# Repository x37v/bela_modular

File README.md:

# bela_modular

A modular level interface for the bela beagle bone black cape, kicad projects.

[bela](http://bela.io/) is a cape for the beagle bone black

* based off the [audio expansion cape](http://blog.bela.io/analogue-vs-digital/)
* [hardware info](https://github.com/BelaPlatform/Bela/wiki/Hardware-explained)

## Pin mappings

The digital i/o is mapped as such:

|Bela #|	 Board            | Note 	             |
|------|---------           | -------------------|
|00    |  in 1              ||
|01    |  in 2              ||
|02    |  in 3              ||
|03    |  in 4              ||
|04    |  digtial in enable | pull low to enable |
|05    |  vfd ctrl enable   | pull low to enable |
|06    |  encin2-btn        ||
|07    |  encin2-b          ||
|08    |  out 1             ||
|09    |  out 2             ||
|10    |  encin2-a          ||
|11    |  out 3             ||
|12    |  out 5             ||
|13    |  out 4             ||
|14    |  out 7             ||
|15    |  out 6             ||

### VFD IO

| P8 |                      | gpio | note                    |
|:--:|----------------------|------|--                       |
| 12 | ctrl enable          | 1_12 | mapped in bela software |
| 14 | digital out enable   | 0_26 |      |
| 31 | P busy in            | 0_10 |      |
| 34 | vDE                  | 2_17 |      |
| 35 | CS2                  | 0_8  |      |
| 36 | CS1                  | 2_16 |      |
| 37 | /RD and RW           | 2_14 |      |
| 38 | /WR and RS           | 2_15 |      |
|    |                      |      |      |
| 39 | D7                   | 2_12 |      |
| 40 | D6                   | 2_13 |      |
| 41 | D5                   | 2_10 |      |
| 42 | D4                   | 2_11 |      |
| 43 | D3                   | 2_8  |      |
| 44 | D2                   | 2_9  |      |
| 45 | D1                   | 2_6  |      |
| 46 | D0                   | 2_7  |      |

### Errors/rework

The digital 'extra' board from 3/17 requires a rework for the digital out and
control enable pins [P8 12 and 14]. These should be detached from 5V and
attached to 3.3V.

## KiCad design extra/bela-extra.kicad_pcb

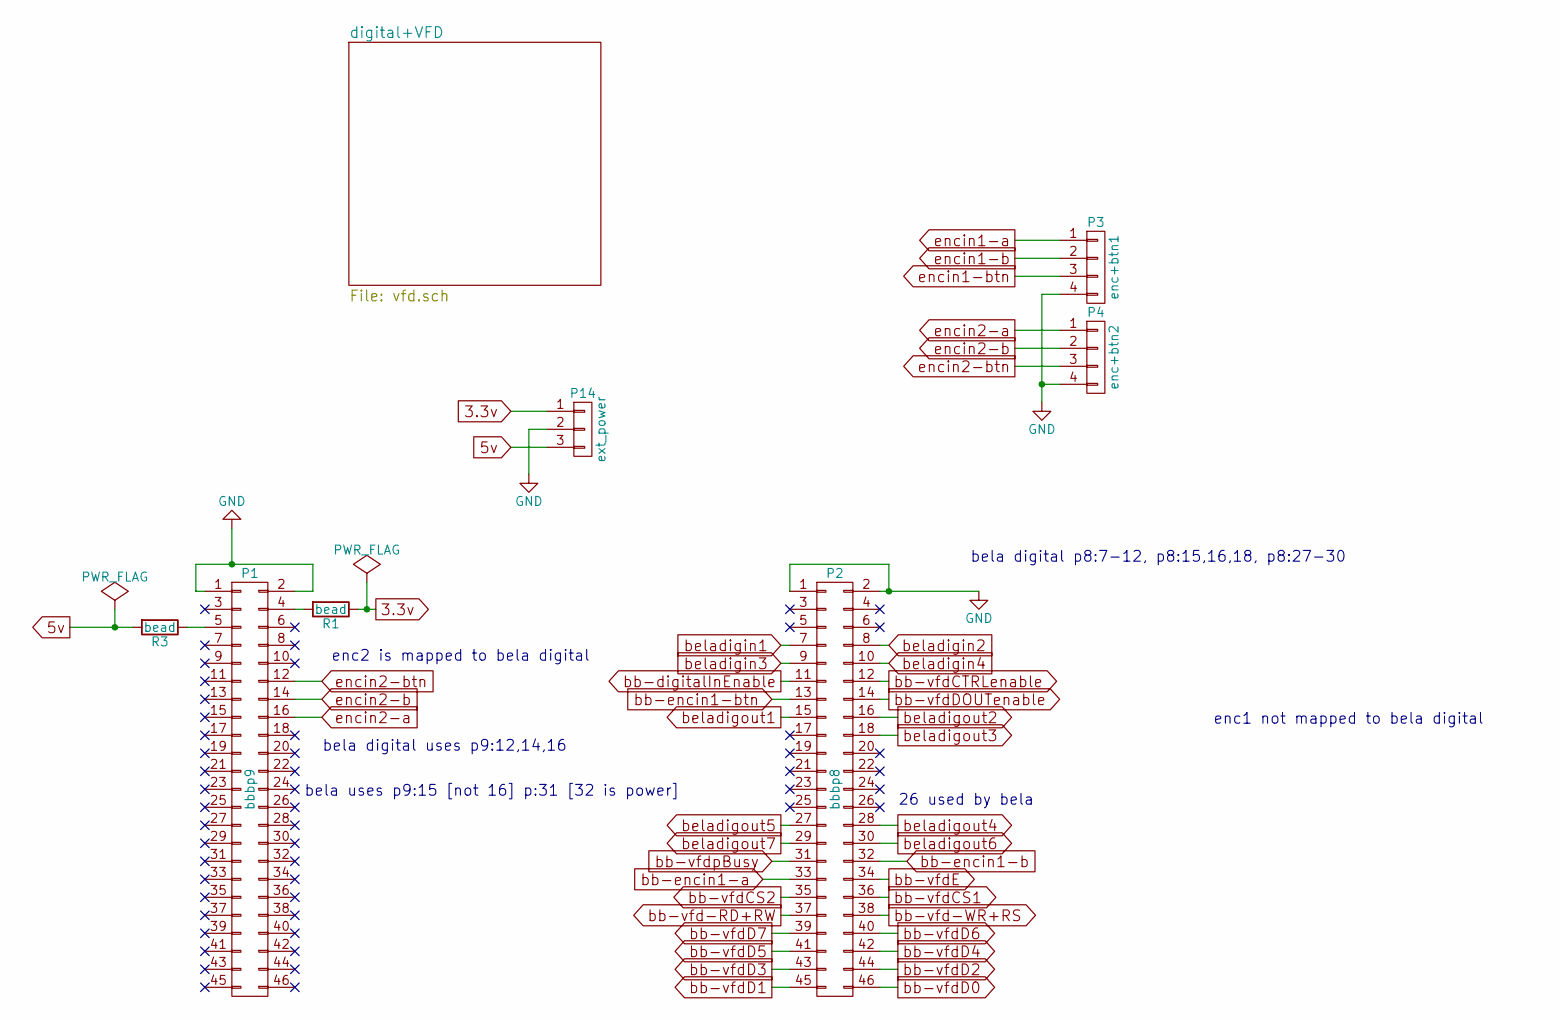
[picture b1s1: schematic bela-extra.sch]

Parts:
P1: bbbp9; Pin_Header_Straight_2x23_Pitch2.54mm
P2: bbbp8; Pin_Header_Straight_2x23_Pitch2.54mm
P3: enc+btn1; Pin_Header_Straight_1x04_Pitch2.54mm
P4: enc+btn2; Pin_Header_Straight_1x04_Pitch2.54mm
P14: ext_power; Pin_Header_Straight_1x03_Pitch2.54mm
R1, R3: bead; Resistor_Vertical_RM5mm-xnor

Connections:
3.3v: P14.1, R1.1; also elsewhere on the board
5v: P14.3, R3.2; also elsewhere on the board
GND: P1.1, P1.2, P2.1, P2.2, P3.4, P4.4, P14.2; also elsewhere on the board
unnamed: P1.4, R1.2
unnamed: P1.5, R3.1
bb-digitalInEnable: P2.11; also elsewhere on the board
bb-encin1-a: P2.33; also elsewhere on the board
bb-encin1-b: P2.32; also elsewhere on the board
bb-encin1-btn: P2.13; also elsewhere on the board
bb-vfd-RD+RW: P2.37; also elsewhere on the board
bb-vfd-WR+RS: P2.38; also elsewhere on the board
bb-vfdCS1: P2.36; also elsewhere on the board
bb-vfdCS2: P2.35; also elsewhere on the board
bb-vfdCTRLenable: P2.12; also elsewhere on the board
bb-vfdD0: P2.46; also elsewhere on the board
bb-vfdD1: P2.45; also elsewhere on the board
bb-vfdD2: P2.44; also elsewhere on the board
bb-vfdD3: P2.43; also elsewhere on the board
bb-vfdD4: P2.42; also elsewhere on the board
bb-vfdD5: P2.41; also elsewhere on the board
bb-vfdD6: P2.40; also elsewhere on the board
bb-vfdD7: P2.39; also elsewhere on the board
bb-vfdDOUTenable: P2.14; also elsewhere on the board
bb-vfdE: P2.34; also elsewhere on the board
bb-vfdpBusy: P2.31; also elsewhere on the board
beladigin1: P2.7; also elsewhere on the board
beladigin2: P2.8; also elsewhere on the board
beladigin3: P2.9; also elsewhere on the board
beladigin4: P2.10; also elsewhere on the board
beladigout1: P2.15; also elsewhere on the board
beladigout2: P2.16; also elsewhere on the board
beladigout3: P2.18; also elsewhere on the board
beladigout4: P2.28; also elsewhere on the board
beladigout5: P2.27; also elsewhere on the board
beladigout6: P2.30; also elsewhere on the board
beladigout7: P2.29; also elsewhere on the board
encin1-a: P3.1; also elsewhere on the board
encin1-b: P3.2; also elsewhere on the board
encin1-btn: P3.3; also elsewhere on the board
encin2-a: P1.16, P4.1
encin2-b: P1.14, P4.2
encin2-btn: P1.12, P4.3

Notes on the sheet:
enc1 not mapped to bela digital
enc2 is mapped to bela digital
26 used by bela
bela uses p9:15 [not 16] p:31 [32 is power]
bela digital p8:7-12, p8:15,16,18, p8:27-30
bela digital uses p9:12,14,16

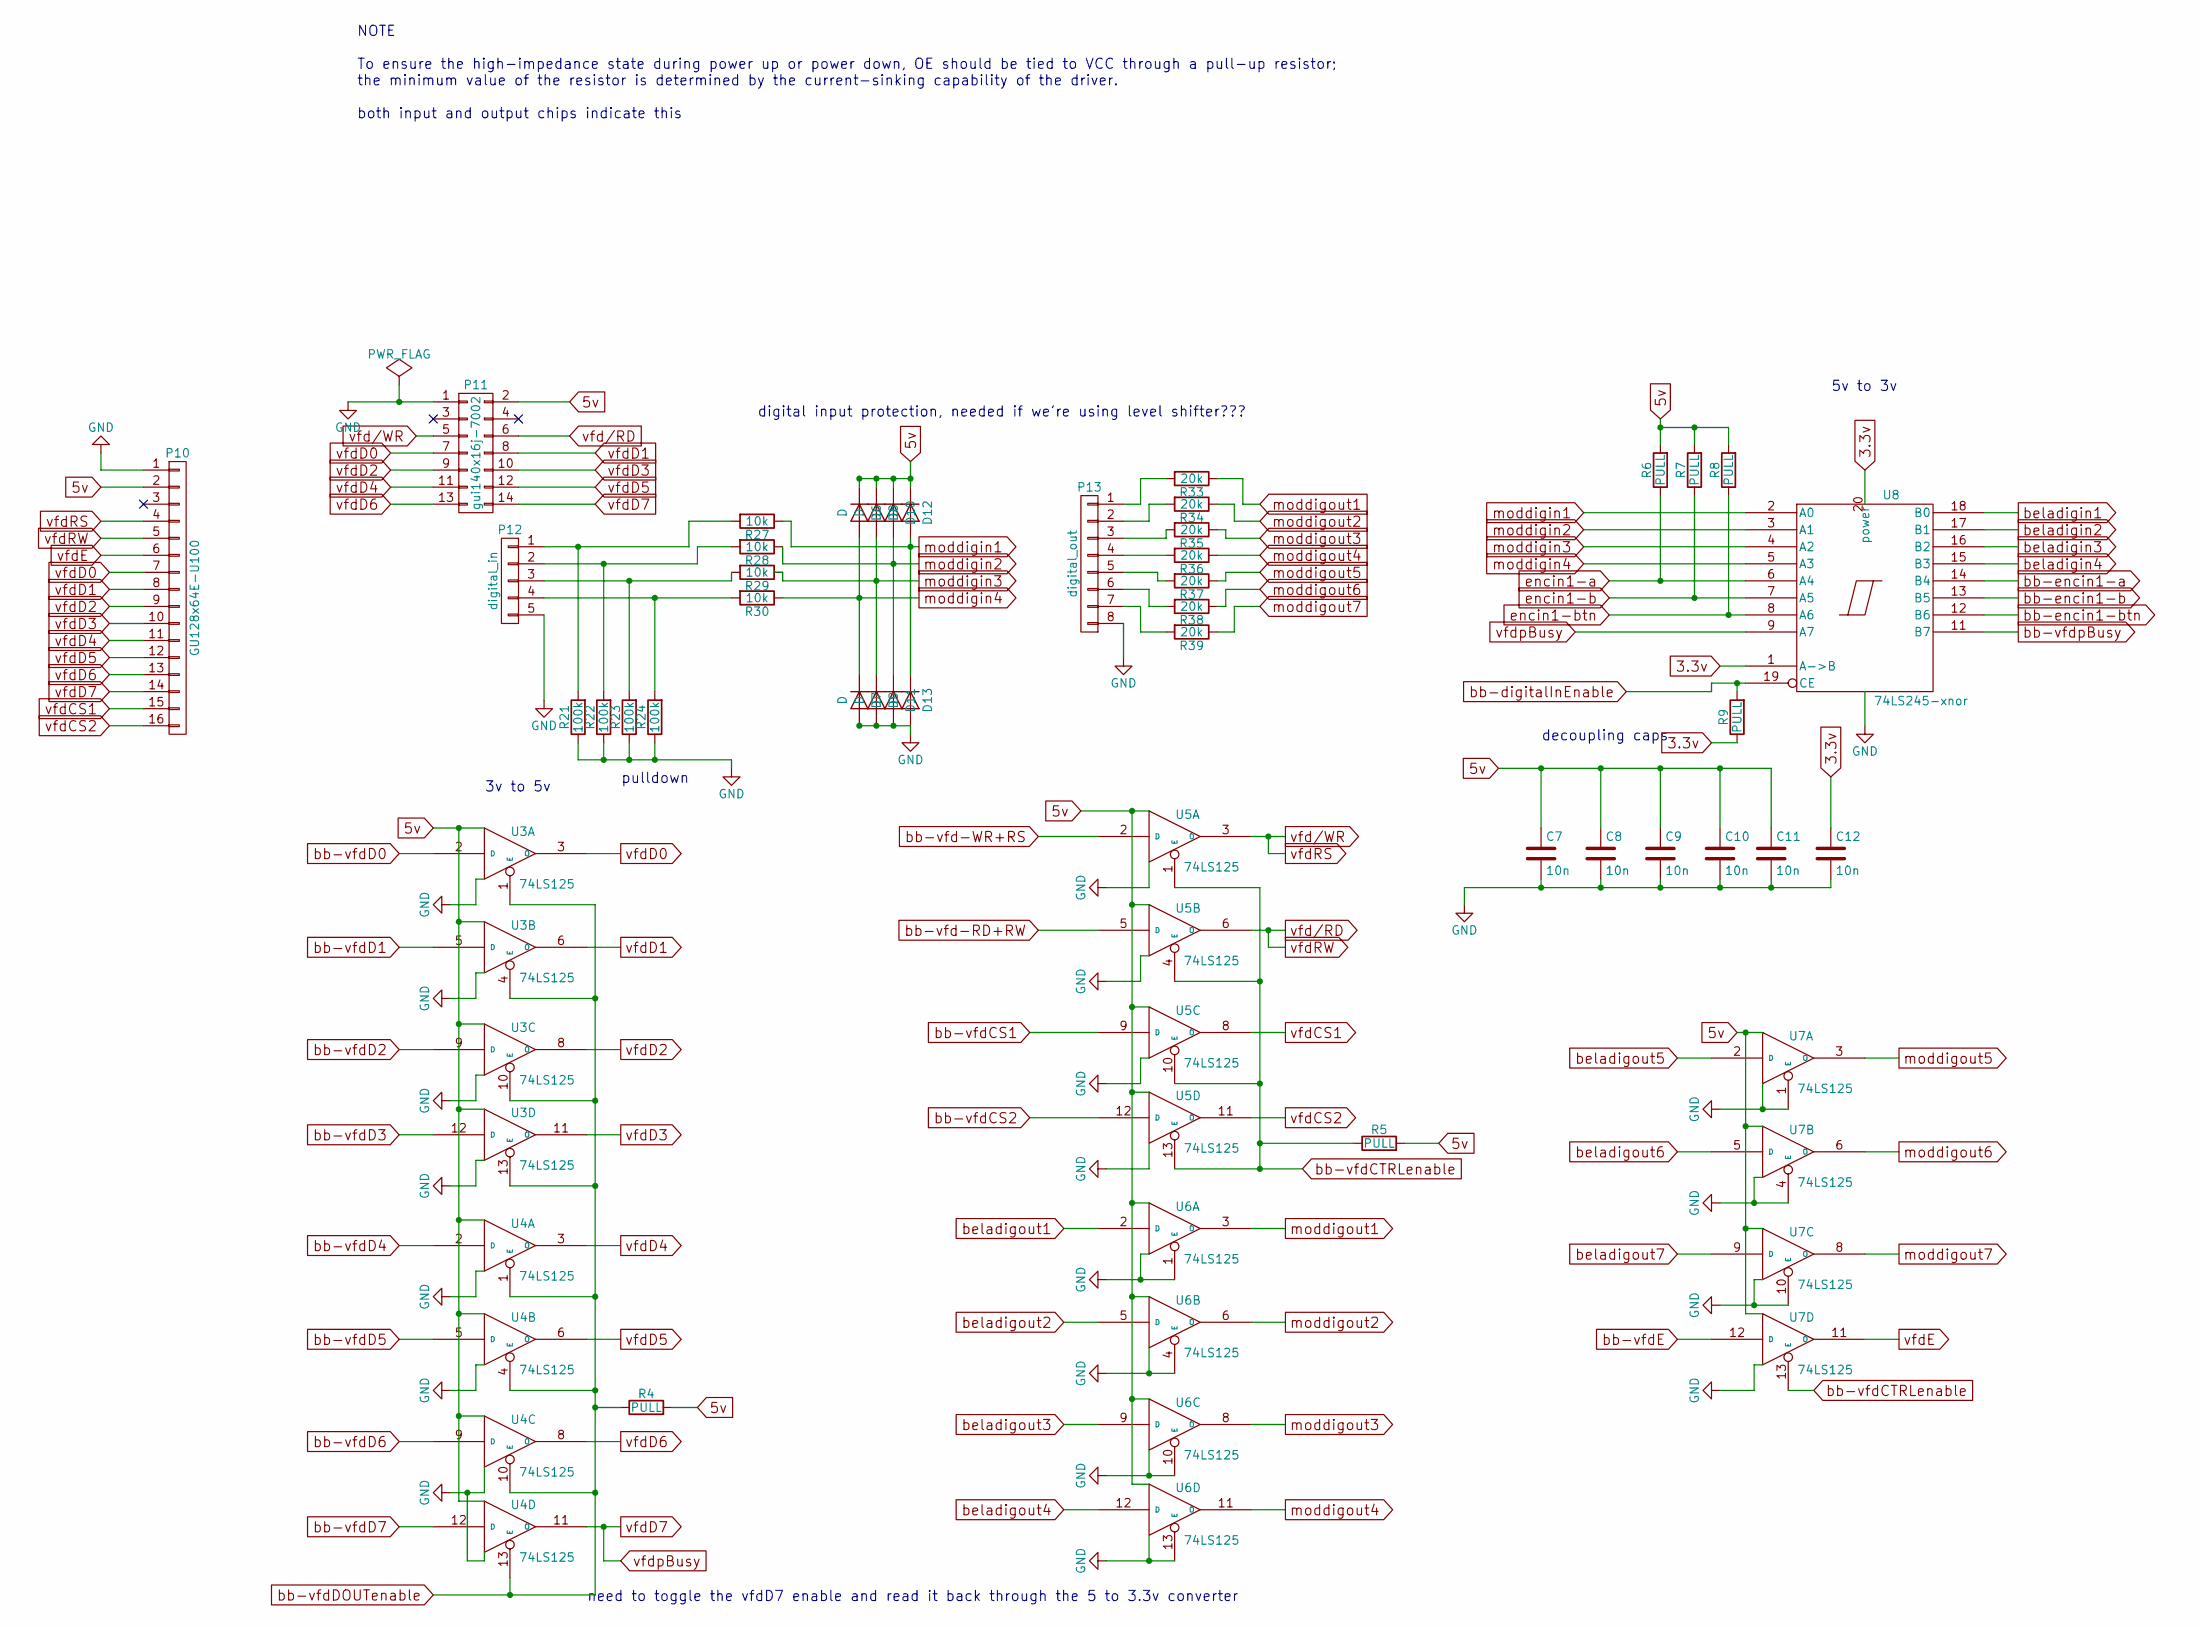
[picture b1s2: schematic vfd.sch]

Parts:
C7, C8, C9, C10, C11, C12: 10n; C_Rect_L4_W2.5_P2.5
D6, D7, D8, D9, D10, D11, D12, D13: D; D_DO-41_SOD81_P7.62mm_Horizontal
P10: GU128x64E-U100; Pin_Header_Straight_1x16_Pitch2.54mm
P11: gui140x16j-7002; Pin_Header_Straight_2x07_Pitch2.54mm
P12: digital_in; Pin_Header_Straight_1x05_Pitch2.54mm
P13: digital_out; Pin_Header_Straight_1x08_Pitch2.54mm
R4, R5, R6, R7, R8, R9: PULL; Resistor_Horizontal_RM10mm-xnorman
R21, R22, R23, R24: 100k; Resistor_Horizontal_RM10mm-xnorman
R27, R28, R29, R30: 10k; Resistor_Horizontal_RM10mm-xnorman
R33, R34, R35, R36, R37, R38, R39: 20k; Resistor_Horizontal_RM10mm-xnorman
U3, U4, U5, U6, U7: 74LS125; DIP-14_W7.62mm_LongPads
U8: 74LS245-xnor; DIP-20_W7.62mm_LongPads

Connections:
3.3v: C12.1, R9.1, U8.1 (A->B), U8.20 (power); also elsewhere on the board
5v: C7.1, C8.1, C9.1, C10.1, C11.1, D6.1 (K), D8.1 (K), D10.1 (K), D12.1 (K), P10.2, P11.2, R4.2, R5.2, R6.2, R7.2, R8.2, U3.14 (VCC), U4.14 (VCC), U5.14 (VCC), U6.14 (VCC), U7.14 (VCC); also elsewhere on the board
GND: C7.2, C8.2, C9.2, C10.2, C11.2, C12.2, D7.2 (A), D9.2 (A), D11.2 (A), D13.2 (A), P10.1, P11.1, P12.5, P13.8, R21.1, R22.1, R23.1, R24.1, U3.7 (GND), U4.7 (GND), U5.7 (GND), U6.1 (E), U6.4 (E), U6.7 (GND), U6.10 (E), U6.13 (E), U7.1 (E), U7.4 (E), U7.7 (GND), U7.10 (E), U8.10 (GND); also elsewhere on the board
unnamed: P12.1, R21.2, R27.2
unnamed: P12.2, R22.2, R28.2
unnamed: P12.3, R23.2, R29.2
unnamed: P12.4, R24.2, R30.2
unnamed: P13.1, R33.2
unnamed: P13.2, R34.2
unnamed: P13.3, R35.2
unnamed: P13.4, R36.2
unnamed: P13.5, R37.2
unnamed: P13.6, R38.2
unnamed: P13.7, R39.2
bb-digitalInEnable: R9.2, U8.19 (CE); also elsewhere on the board
bb-encin1-a: U8.14 (B4); also elsewhere on the board
bb-encin1-b: U8.13 (B5); also elsewhere on the board
bb-encin1-btn: U8.12 (B6); also elsewhere on the board
bb-vfd-RD+RW: U5.5 (D); also elsewhere on the board
bb-vfd-WR+RS: U5.2 (D); also elsewhere on the board
bb-vfdCS1: U5.9 (D); also elsewhere on the board
bb-vfdCS2: U5.12 (D); also elsewhere on the board
bb-vfdCTRLenable: R5.1, U5.1 (E), U5.4 (E), U5.10 (E), U5.13 (E), U7.13 (E); also elsewhere on the board
bb-vfdD0: U3.2 (D); also elsewhere on the board
bb-vfdD1: U3.5 (D); also elsewhere on the board
bb-vfdD2: U3.9 (D); also elsewhere on the board
bb-vfdD3: U3.12 (D); also elsewhere on the board
bb-vfdD4: U4.2 (D); also elsewhere on the board
bb-vfdD5: U4.5 (D); also elsewhere on the board
bb-vfdD6: U4.9 (D); also elsewhere on the board
bb-vfdD7: U4.12 (D); also elsewhere on the board
bb-vfdDOUTenable: R4.1, U3.1 (E), U3.4 (E), U3.10 (E), U3.13 (E), U4.1 (E), U4.4 (E), U4.10 (E), U4.13 (E); also elsewhere on the board
bb-vfdE: U7.12 (D); also elsewhere on the board
bb-vfdpBusy: U8.11 (B7); also elsewhere on the board
beladigin1: U8.18 (B0); also elsewhere on the board
beladigin2: U8.17 (B1); also elsewhere on the board
beladigin3: U8.16 (B2); also elsewhere on the board
beladigin4: U8.15 (B3); also elsewhere on the board
beladigout1: U6.2 (D); also elsewhere on the board
beladigout2: U6.5 (D); also elsewhere on the board
beladigout3: U6.9 (D); also elsewhere on the board
beladigout4: U6.12 (D); also elsewhere on the board
beladigout5: U7.2 (D); also elsewhere on the board
beladigout6: U7.5 (D); also elsewhere on the board
beladigout7: U7.9 (D); also elsewhere on the board
encin1-a: R6.1, U8.6 (A4); also elsewhere on the board
encin1-b: R7.1, U8.7 (A5); also elsewhere on the board
encin1-btn: R8.1, U8.8 (A6); also elsewhere on the board
moddigin1: D12.2 (A), D13.1 (K), R27.1, U8.2 (A0)
moddigin2: D10.2 (A), D11.1 (K), R28.1, U8.3 (A1)
moddigin3: D8.2 (A), D9.1 (K), R29.1, U8.4 (A2)
moddigin4: D6.2 (A), D7.1 (K), R30.1, U8.5 (A3)
moddigout1: R33.1, U6.3 (O)
moddigout2: R34.1, U6.6 (O)
moddigout3: R35.1, U6.8 (O)
moddigout4: R36.1, U6.11 (O)
moddigout5: R37.1, U7.3 (O)
moddigout6: R38.1, U7.6 (O)
moddigout7: R39.1, U7.8 (O)
vfd/RD: P10.5, P11.6, U5.6 (O)
vfd/WR: P10.4, P11.5, U5.3 (O)
vfdCS1: P10.15, U5.8 (O)
vfdCS2: P10.16, U5.11 (O)
vfdD0: P10.7, P11.7, U3.3 (O)
vfdD1: P10.8, P11.8, U3.6 (O)
vfdD2: P10.9, P11.9, U3.8 (O)
vfdD3: P10.10, P11.10, U3.11 (O)
vfdD4: P10.11, P11.11, U4.3 (O)
vfdD5: P10.12, P11.12, U4.6 (O)
vfdD6: P10.13, P11.13, U4.8 (O)
vfdD7: P10.14, P11.14, U4.11 (O), U8.9 (A7)
vfdE: P10.6, U7.11 (O)

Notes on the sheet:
3v to 5v
5v to 3v
need to toggle the vfdD7 enable and read it back through the 5 to 3.3v converter
NOTE To ensure the high-impedance state during power up or power down, OE should be tied to VCC through a pull-up resistor; the minimum value of the resistor is determined by the current-sinking capability of the driver. both input and output chips indicate this
digital input protection, needed if we're using level shifter???
pulldown
decoupling caps

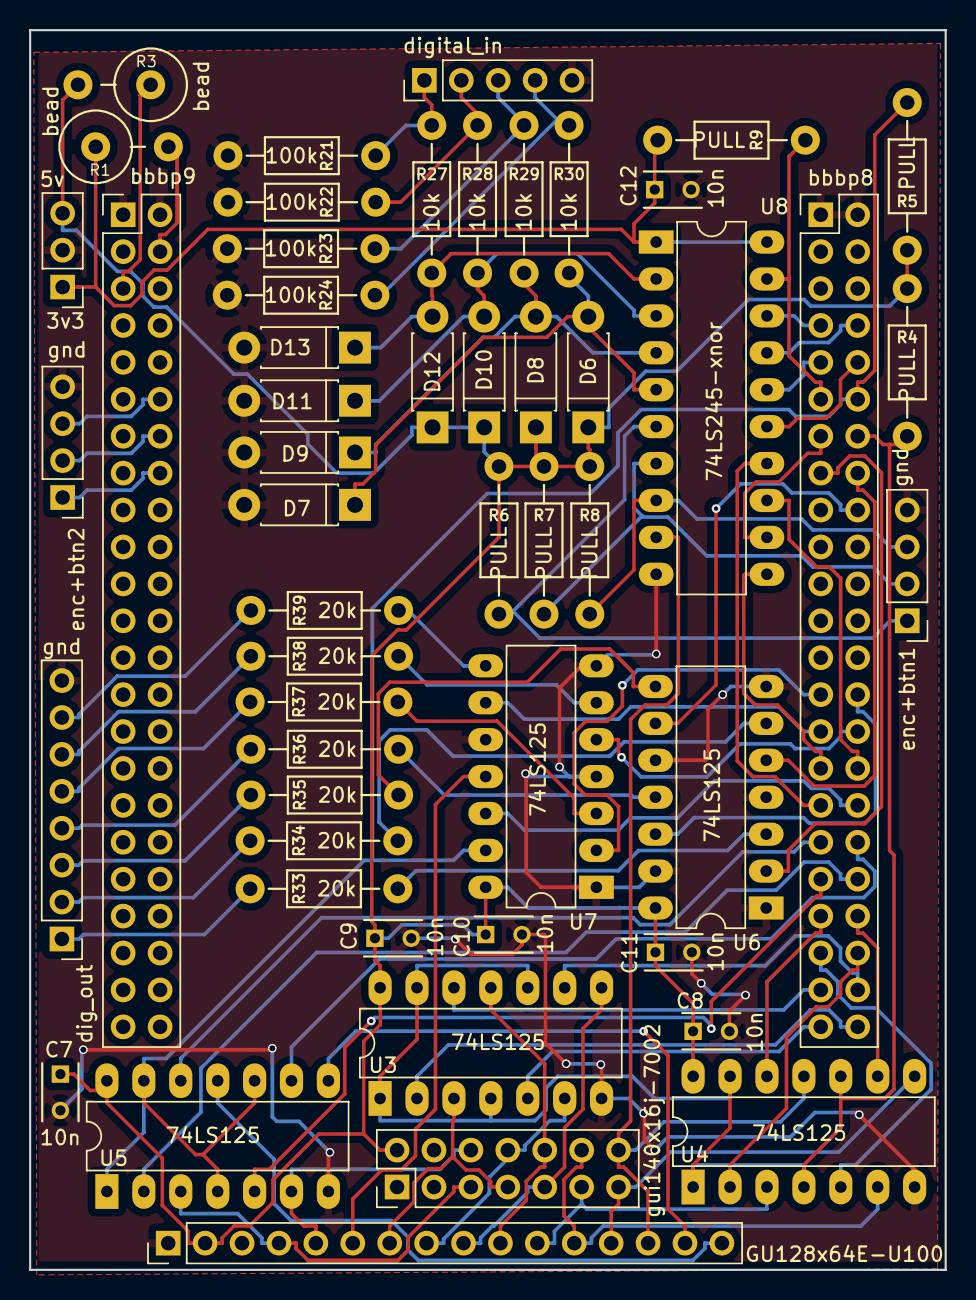
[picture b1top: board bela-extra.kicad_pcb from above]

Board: 2 copper layers, 63.0 x 85.3 mm, 52 parts (0 on the bottom side), 77 nets.

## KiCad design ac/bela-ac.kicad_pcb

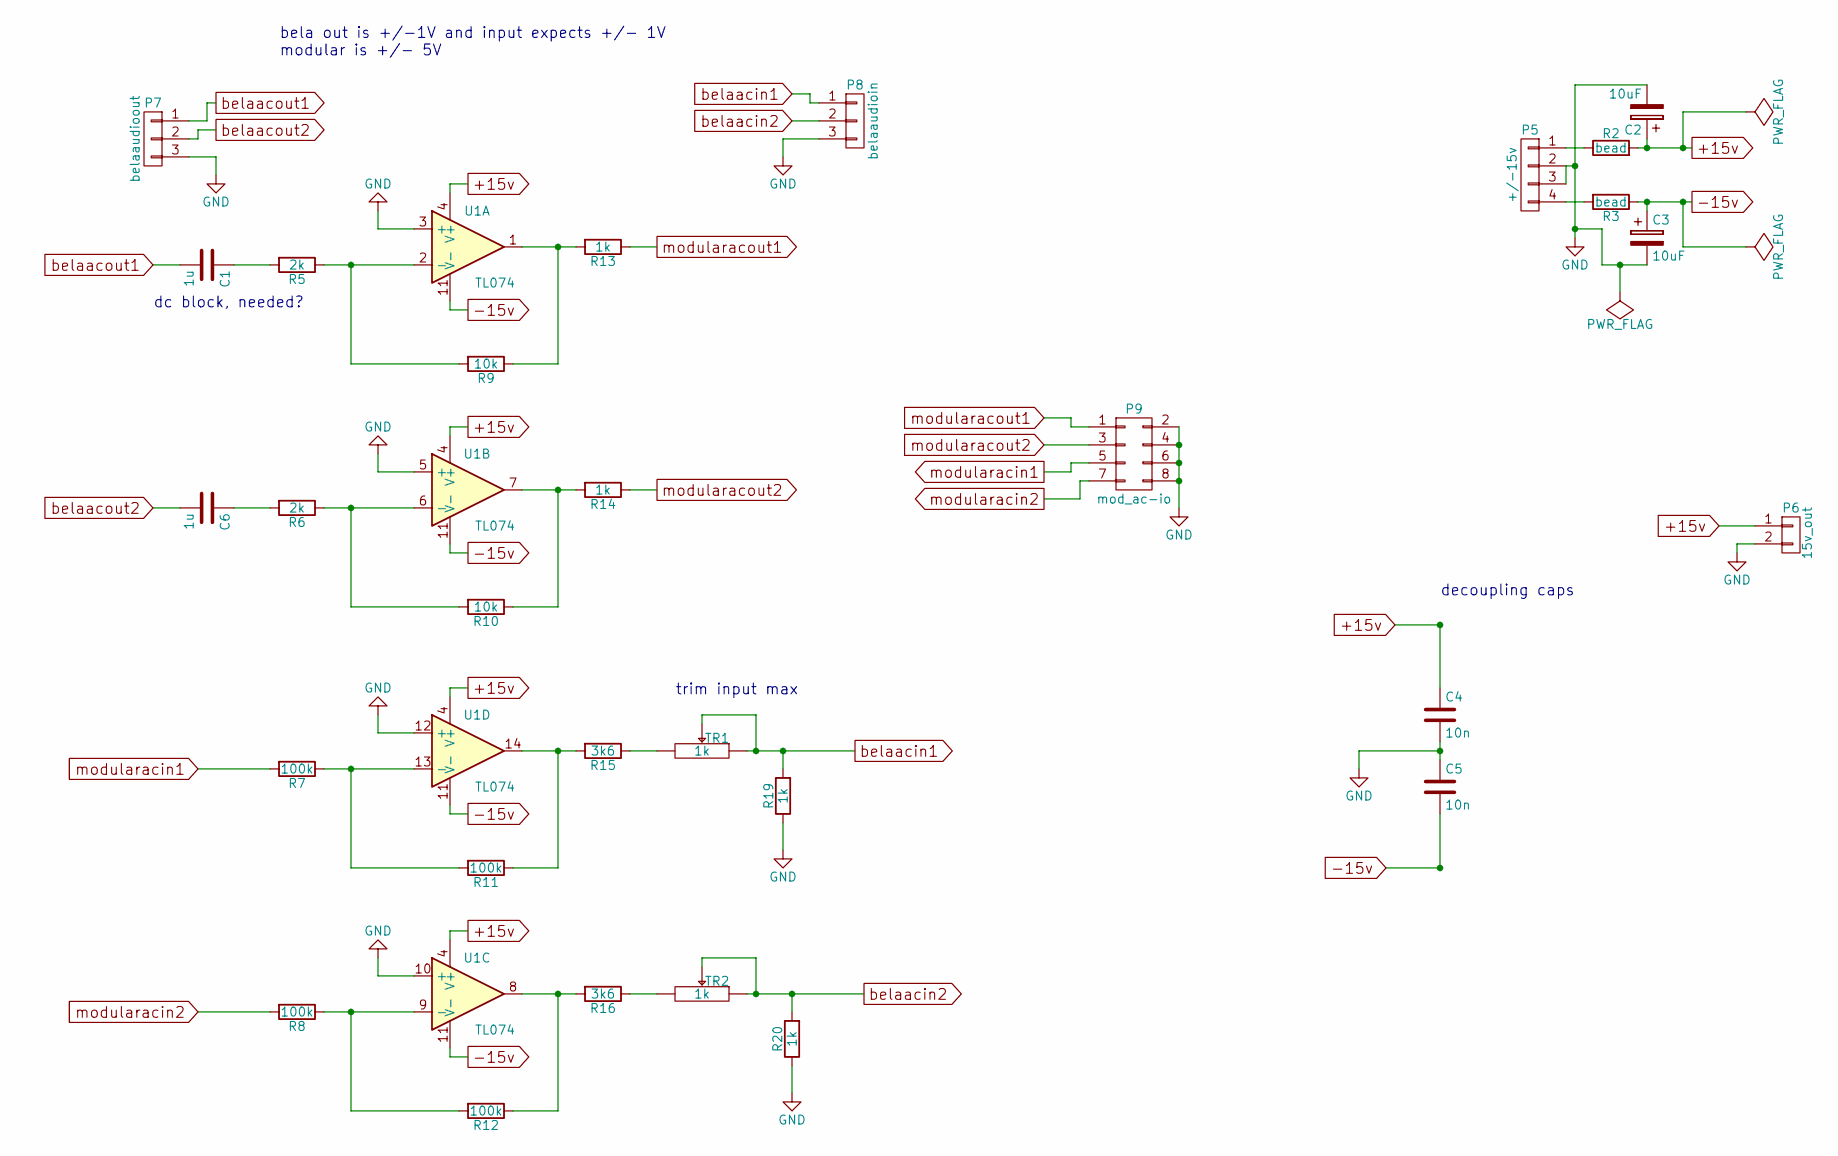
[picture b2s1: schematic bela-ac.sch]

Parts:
C1, C6: 1u; C_Rect_L4_W2.5_P2.5
C2, C3: 10uF; C_Radial_D5_L11_P2
C4, C5: 10n; C_Rect_L4_W2.5_P2.5
P5: +/-15v; MTA-156-4
P6: 15v_out; MTA-156-2
P7: belaaudioout; Pin_Header_Straight_1x03_Pitch2.54mm
P8: belaaudioin; Pin_Header_Straight_1x03_Pitch2.54mm
P9: mod_ac-io; Pin_Header_Straight_2x04_Pitch2.54mm
R2, R3: bead; Resistor_Vertical_RM5mm-xnor
R5, R6: 2k; Resistor_Horizontal_RM10mm-xnorman
R7, R8, R11, R12: 100k; Resistor_Horizontal_RM10mm-xnorman
R9, R10: 10k; Resistor_Horizontal_RM10mm-xnorman
R13, R14, R19, R20: 1k; Resistor_Horizontal_RM10mm-xnorman
R15, R16: 3k6; Resistor_Horizontal_RM10mm-xnorman
TR1, TR2: 1k; trimmer
U1: TL074; DIP-14_W7.62mm_LongPads

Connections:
+15v: C2.1, C4.1, P6.1, R2.2, U1.4 (V+)
-15v: C3.1, C5.2, R3.1, U1.11 (V-)
GND: C2.2, C3.2, C4.2, C5.1, P5.2, P5.3, P6.2, P7.3, P8.3, P9.2, P9.4, P9.6, P9.8, R19.1, R20.1, U1.3 (+), U1.5 (+), U1.10 (+), U1.12 (+)
unnamed: C1.1, R5.2
unnamed: C6.1, R6.2
unnamed: P5.1, R2.1
unnamed: P5.4, R3.2
unnamed: R5.1, R9.2, U1.2 (-)
unnamed: R10.1, R14.2, U1.7
unnamed: R6.1, R10.2, U1.6 (-)
unnamed: R11.1, R15.2, U1.14
unnamed: R7.1, R11.2, U1.13 (-)
unnamed: R12.1, R16.2, U1.8
unnamed: R8.1, R12.2, U1.9 (-)
unnamed: R9.1, R13.2, U1.1
unnamed: R15.1, TR1.3
unnamed: R16.1, TR2.3
belaacin1: P8.1, R19.2, TR1.1, TR1.2
belaacin2: P8.2, R20.2, TR2.1, TR2.2
belaacout1: C1.2, P7.1
belaacout2: C6.2, P7.2
modularacin1: P9.5, R7.2
modularacin2: P9.7, R8.2
modularacout1: P9.1, R13.1
modularacout2: P9.3, R14.1

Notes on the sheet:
bela out is +/-1V and input expects +/- 1V modular is +/- 5V
decoupling caps
trim input max
dc block, needed?

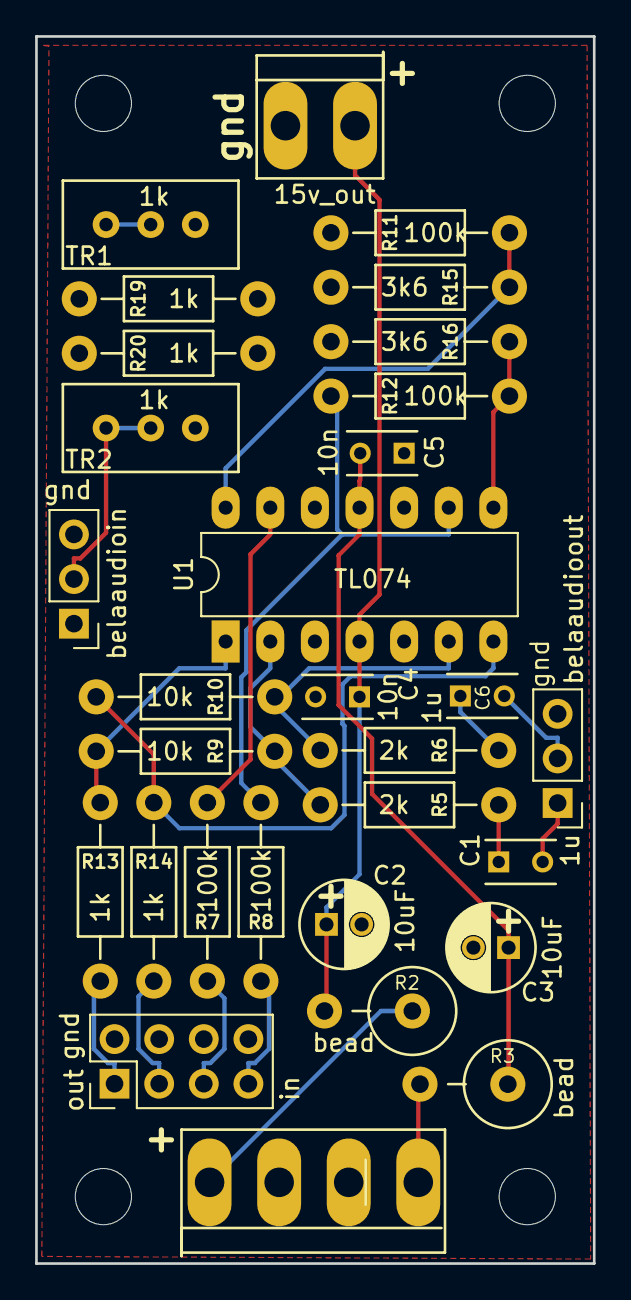
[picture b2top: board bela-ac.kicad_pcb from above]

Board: 2 copper layers, 31.8 x 69.9 mm, 34 parts (0 on the bottom side), 25 nets.

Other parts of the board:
REF1, REF2, REF3, REF4: MountingHole_3.2mm_M3

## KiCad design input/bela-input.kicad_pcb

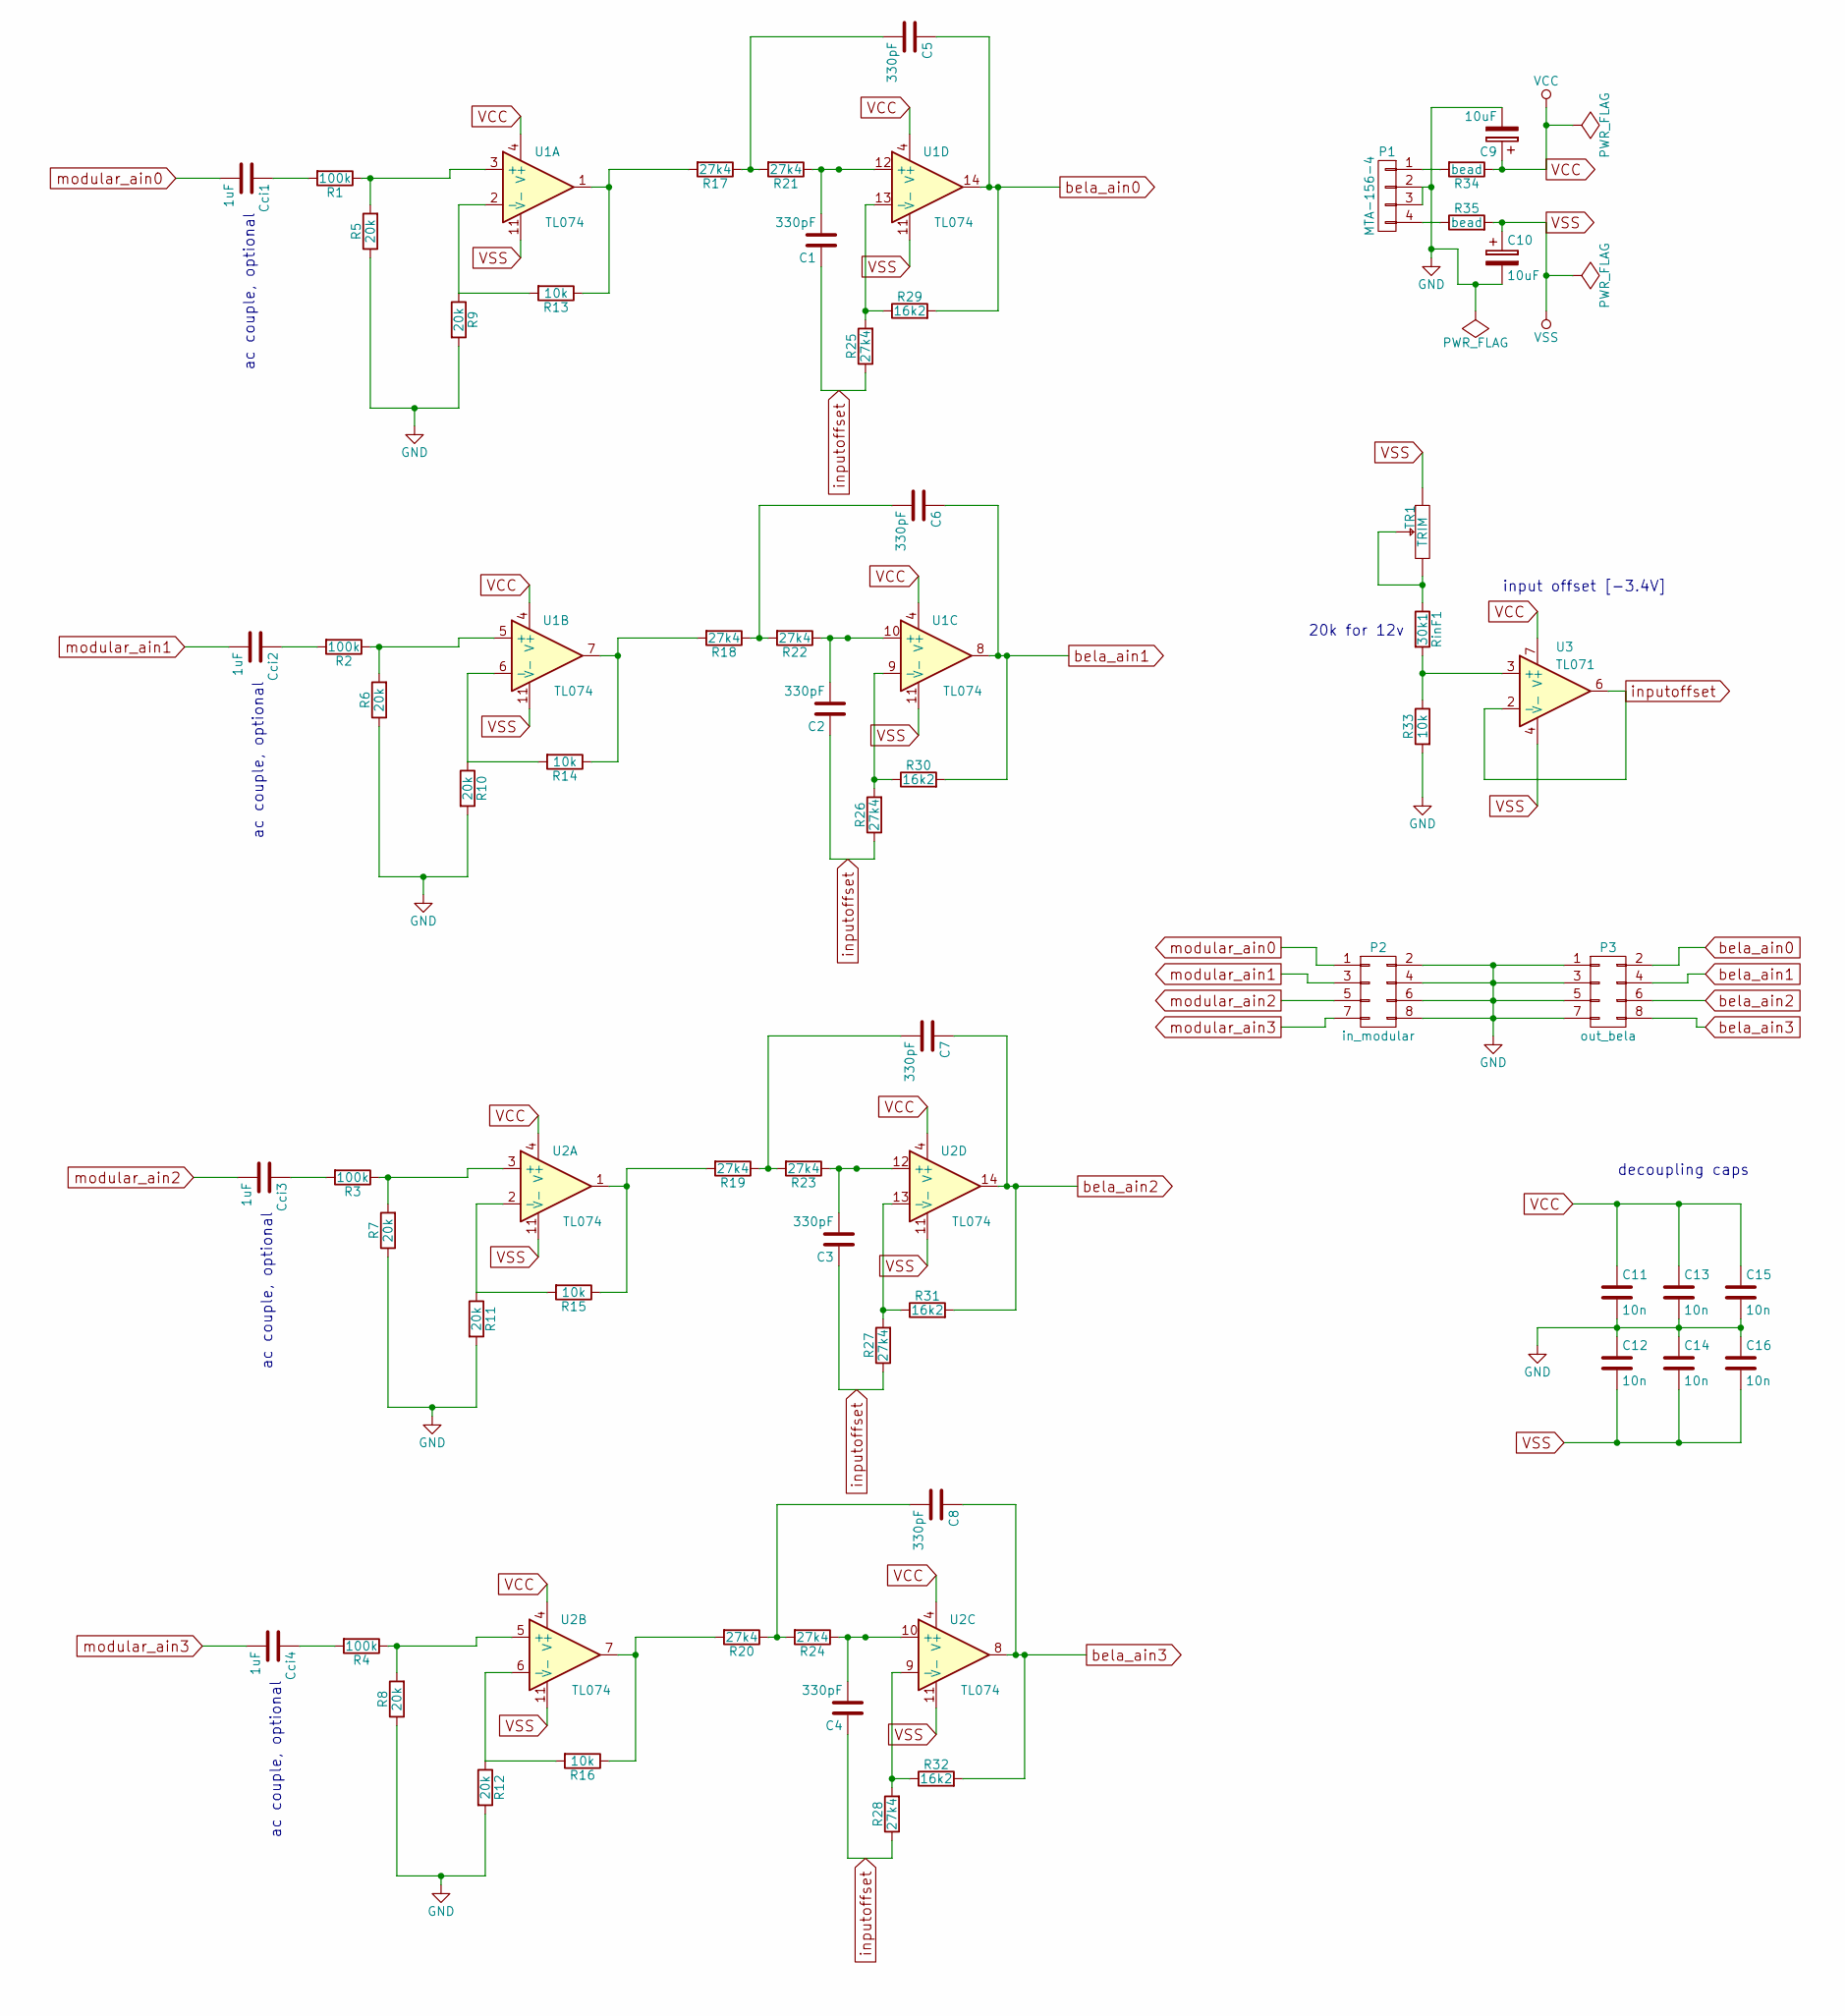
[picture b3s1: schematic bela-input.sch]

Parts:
C1, C2, C3, C4, C5, C6, C7, C8: 330pF; C_Rect_L4_W2.5_P2.5
C9, C10: 10uF; C_Radial_D5_L11_P2
C11, C12, C13, C14, C15, C16: 10n; C_Rect_L4_W2.5_P2.5
Cci1, Cci2, Cci3, Cci4: 1uF; C_Rect_L4_W2.5_P2.5
P1: MTA-156-4
P2: in_modular; Pin_Header_Straight_2x04
P3: out_bela; Pin_Header_Straight_2x04
R1, R2, R3, R4: 100k; Resistor_Horizontal_RM10mm-xnorman
R5, R6, R7, R8, R9, R10, R11, R12: 20k; Resistor_Horizontal_RM10mm-xnorman
R13, R14, R15, R16, R33: 10k; Resistor_Horizontal_RM10mm-xnorman
R17, R18, R19, R20, R21, R22, R23, R24, R25, R26, R27, R28: 27k4; Resistor_Horizontal_RM10mm-xnorman
R29, R30, R31, R32: 16k2; Resistor_Horizontal_RM10mm-xnorman
R34, R35: bead; Resistor_Vertical_RM5mm-xnor
RinF1: 30k1; Resistor_Horizontal_RM10mm-xnorman
TR1: TRIM; trimmer
U1, U2: TL074; DIP-14_W7.62mm_LongPads
U3: TL071; DIP-8_W7.62mm_LongPads

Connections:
GND: C9.2, C10.2, C11.2, C12.1, C13.2, C14.1, C15.2, C16.1, P1.2, P1.3, P2.2, P2.4, P2.6, P2.8, P3.1, P3.3, P3.5, P3.7, R5.1, R6.1, R7.1, R8.1, R9.2, R10.2, R11.2, R12.2, R33.2
unnamed: C1.2, R21.1, U1.12 (+)
unnamed: C2.2, R22.1, U1.10 (+)
unnamed: C3.2, R23.1, U2.12 (+)
unnamed: C4.2, R24.1, U2.10 (+)
unnamed: C5.2, R17.1, R21.2
unnamed: C6.2, R18.1, R22.2
unnamed: C7.2, R19.1, R23.2
unnamed: C8.2, R20.1, R24.2
unnamed: Cci1.1, R1.2
unnamed: Cci2.1, R2.2
unnamed: Cci3.1, R3.2
unnamed: Cci4.1, R4.2
unnamed: P1.1, R34.2
unnamed: P1.4, R35.1
unnamed: R1.1, R5.2, U1.3 (+)
unnamed: R2.1, R6.2, U1.5 (+)
unnamed: R3.1, R7.2, U2.3 (+)
unnamed: R4.1, R8.2, U2.5 (+)
unnamed: R10.1, R14.2, U1.6 (-)
unnamed: R11.1, R15.2, U2.2 (-)
unnamed: R12.1, R16.2, U2.6 (-)
unnamed: R13.1, R17.2, U1.1
unnamed: R9.1, R13.2, U1.2 (-)
unnamed: R14.1, R18.2, U1.7
unnamed: R15.1, R19.2, U2.1
unnamed: R16.1, R20.2, U2.7
unnamed: R25.2, R29.1, U1.13 (-)
unnamed: R26.2, R30.1, U1.9 (-)
unnamed: R27.2, R31.1, U2.13 (-)
unnamed: R28.2, R32.1, U2.9 (-)
unnamed: R33.1, RinF1.2, U3.3 (+)
unnamed: RinF1.1, TR1.2, TR1.3
VCC: C9.1, C11.1, C13.1, C15.1, R34.1, U1.4 (V+), U2.4 (V+), U3.7 (V+)
VSS: C10.1, C12.2, C14.2, C16.2, R35.2, TR1.1, U1.11 (V-), U2.11 (V-), U3.4 (V-)
bela_ain0: C5.1, P3.2, R29.2, U1.14
bela_ain1: C6.1, P3.4, R30.2, U1.8
bela_ain2: C7.1, P3.6, R31.2, U2.14
bela_ain3: C8.1, P3.8, R32.2, U2.8
inputoffset: C1.1, C2.1, C3.1, C4.1, R25.1, R26.1, R27.1, R28.1, U3.2 (-), U3.6
modular_ain0: Cci1.2, P2.1
modular_ain1: Cci2.2, P2.3
modular_ain2: Cci3.2, P2.5
modular_ain3: Cci4.2, P2.7

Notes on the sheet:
ac couple, optional
20k for 12v
input offset [-3.4V]
decoupling caps

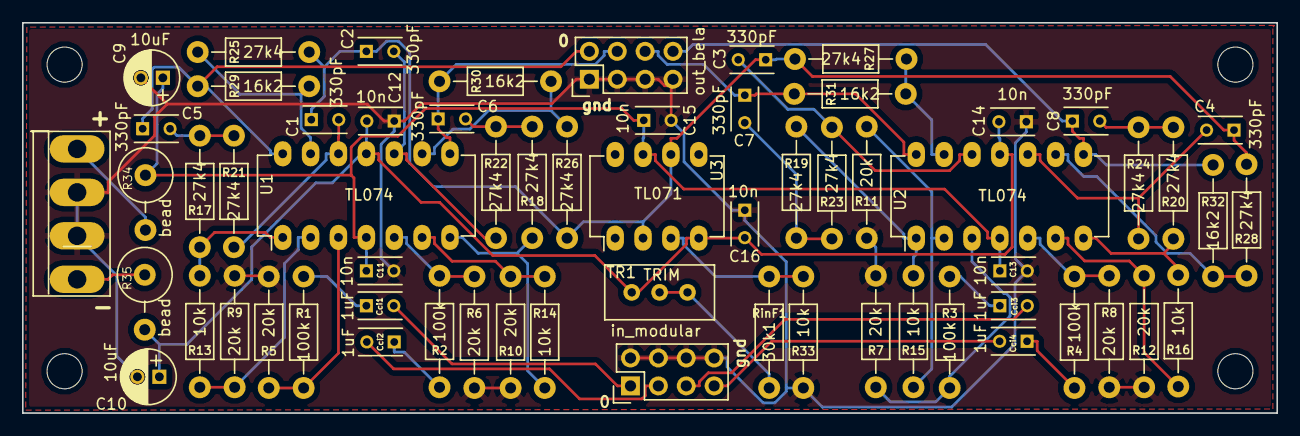
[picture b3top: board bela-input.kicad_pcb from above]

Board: 2 copper layers, 114.3 x 35.6 mm, 67 parts (0 on the bottom side), 44 nets.

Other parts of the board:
REF1, REF2, REF3, REF4: MountingHole_3.2mm_M3
